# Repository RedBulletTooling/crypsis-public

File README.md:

This project has been created and developed by Matthijs Vogel and Luc Pluimakers.

# Contents of repo
This repo contains all hardware and software files to recreate Crypsis.

Detailed documenatation can be found on our gitbook link here: https://redbullettooling.gitbook.io/keyvilboard-apt/

# Motivation
We would hate to see the knowledge that we build up gone to waste, given we decided to halt this product. This product has not been as commercially viable as we had hoped. But we have put time, effort and a decent chunk of money into this project to create something that hasn't been replicated since. Our goal with publicizing this project is that goal of it's creation will be reached. To prevent harms to those who can't protect themselves. May that be terrorism, child exploitation or other crimes. If you work for an organisation that has these same goals and have a need, contact us. We are happy to help.

# What is Crypsis
Crypsis is a hardware keylogger that communicates using a NFR9160 module. By doing so we can do very advanced methods of communicating covertly, aswell as propper implementation of encryption and other security measures. Apart from the hardware the server is dockerized, meaning it's modular and highly adjustable.

Copied from our website (menura.org);

Hardware
- Every chip, fully programmable, fully open-source. 4G (NB-iot/LTE-M) with encrypted TLS/SSL communication and authentication.
- Secure modem with the latest anti-tamper measurements.
- Only communicate, when you want it. True silent mode, undectectable on the RF spectrum.
- Remotely disable the keyboard for damage prevention on entry.

Software
- Fully dockerized server setup, fully open-source. Setup a standalone Crypsis C2 in under minutes.
- Customize and integrate the API to your needs.
- Everything encrypted, with integrated TLS/SSL based authentication.
- Server infrastructure is modular. The direct communication server can be placed in the target country, whilst all sensitive datastorage is kept within your own borders.

USB
- Crypsis device that sits between the PC USB and the USB cable of the keyboard.

Embedded
- Crypsis device that is integrated in the keyboard of choice with soldering. Keep in mind you have to be directly on the USB bus of the keyboard.

# Disclaimer

The code was still heavily under development and under testing (alpha), before deciding to stall the project. There are serious security issues present in this repository. Think, weak default passwords or injection vulnerabilities. Expect potential issues / conflicts.

Apache2 license applies.

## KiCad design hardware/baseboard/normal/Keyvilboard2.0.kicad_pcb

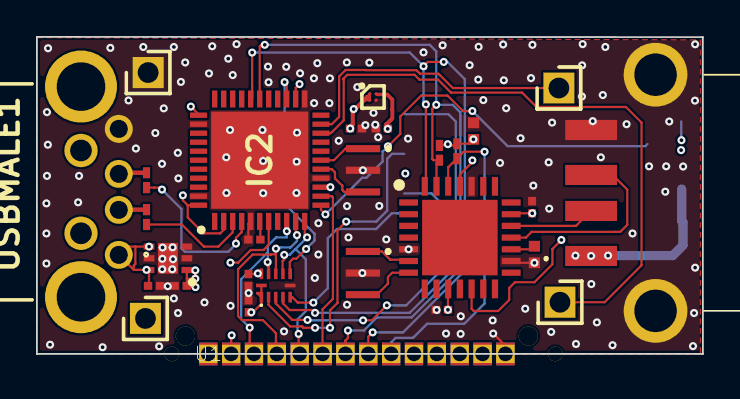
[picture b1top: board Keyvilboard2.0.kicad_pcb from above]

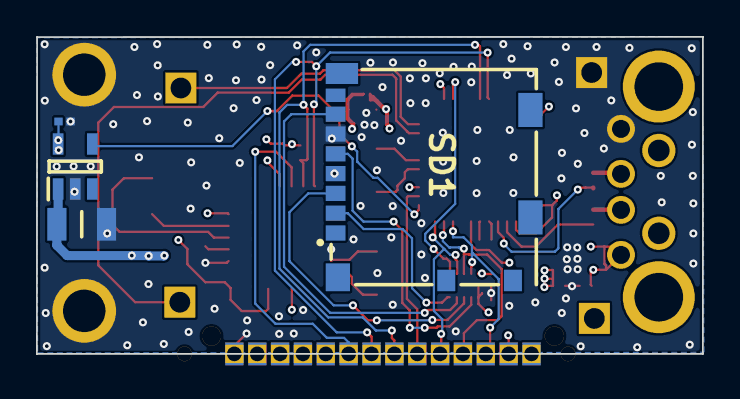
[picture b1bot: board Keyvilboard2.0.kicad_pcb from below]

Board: 4 copper layers, 37.0 x 17.6 mm, 33 parts (4 on the bottom side), 32 nets.

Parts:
0.1uF1, 0.1uF2, 0.1uF5: 02016D104KAT2A; CAPC0603X33N
0.1uF3, 0.1uF4, 1uF1, 1uF2, 1uF3, 1uF4, 1uF5: GRM033C80J105ME05D; CAPC0603X33N
5V+1: 4-103327-3; HDRV1W66P0X254_1X1_213X234X813P
10KOhm1, 10KOhm2: ERA-1AEB103C; RESC0603X26N
10uF1, 10uF2: GRM155C80J106ME11D; CAPC1005X55N
16Mhz1, 16Mhz2: CSTNE16M0VH3C000R0
22Ohm1, 22Ohm2: RC0201JR-7D22RL; RESC0603X26N
C1: GRM31CR60J157ME11L; CAPC3216X180N
GND1: 4-103327-3; HDRV1W66P0X254_1X1_213X234X813P
IC2: ATMEGA32U4-MU; QFN50P700X700X100-45N-D
IC3: PIC24FJ64GB002-I_ML; QFN65P600X600X100-29N-D
IC4: TCR5RG33A,LF; BGA4C35P2X2_64X64X33
IC5: TXB0104RUTR_0; TXB0104RUTR
KEYPWR1: TPS2041CDBVT; SOT95P280X145-5N
PS1: LP5912-5.0DRVR; SON65P200X200X80-7N
RX1: 4-103327-3; HDRV1W66P0X254_1X1_213X234X813P
SD1: 104031-0811; 1040310811
TX1: 4-103327-3; HDRV1W66P0X254_1X1_213X234X813P
U1: EC14-2AP
USBFEMALE1: 87583-2010RLF; 875832010RLF
USBMALE1: UP2-AH-1-TH

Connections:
+3V3: 0.1uF1.1, 0.1uF3.2, 0.1uF4.1, 1uF4.2, 10KOhm1.1, 10KOhm2.2, 10uF2.1, IC3.10, IC3.20, IC3.25, IC4.A2, IC5.1, IC5.12, IC5.13, SD1.4, U1.2
+5V: 1uF3.2, 5V+1.1, PS1.4, PS1.6, USBMALE1.1
CLK: IC5.2, SD1.5
CS: IC5.5, SD1.2
D11: IC2.12, KEYPWR1.4
D+AT: 22Ohm2.1, USBMALE1.3
D+US: IC3.18, USBFEMALE1.3
D-AT: 22Ohm1.1, USBMALE1.2
D-US: IC3.19, USBFEMALE1.2
DI: IC5.3, SD1.3
DO: IC5.4, SD1.7
GND: 0.1uF1.2, 0.1uF2.2, 0.1uF3.1, 0.1uF4.2, 0.1uF5.2, 1uF1.1, 1uF2.1, 1uF3.1, 1uF4.1, 1uF5.1, 10uF1.2, 10uF2.2, 16Mhz1.2, 16Mhz2.2, C1.2, GND1.1, IC2.5, IC2.15, IC2.23, IC2.35, IC2.43, IC2.45, IC3.5, IC3.16, IC3.24, IC4.B2, IC5.6, KEYPWR1.2, PS1.2, PS1.3, PS1.5, PS1.7, SD1.6, U1.14, USBFEMALE1.4, USBFEMALE1.MH1, USBFEMALE1.MH2, USBMALE1.4
MCLR: 10KOhm2.1, IC3.26, U1.9
MISO: IC2.11, IC5.8, U1.5
MOSI: IC2.10, IC5.9, U1.4
NRFRX: IC2.20, RX1.1
NRFTX: IC2.21, TX1.1
unnamed: 1uF1.2, IC2.6
unnamed: 10uF1.1, IC3.17
unnamed: 16Mhz1.1, IC2.17
unnamed: 16Mhz1.3, IC2.16
unnamed: 16Mhz2.1, IC3.6
unnamed: 16Mhz2.3, IC3.7
unnamed: 22Ohm1.2, IC2.3
unnamed: 22Ohm2.2, IC2.4
RST: IC2.13, U1.6
RXUSBH-PGRDATA: 10KOhm1.2, IC2.28, IC3.27, U1.7
SCLK: IC2.9, IC5.10, U1.3
SS: IC2.25, IC5.7
TXUSBH-PGRCLK: IC2.29, IC3.28, U1.8
VCC: 0.1uF2.1, 0.1uF5.1, 1uF2.2, 1uF5.2, IC2.2, IC2.7, IC2.14, IC2.24, IC2.34, IC2.44, IC3.12, IC4.A1, IC4.B1, IC5.11, KEYPWR1.5, PS1.1, U1.1
VDC: C1.1, KEYPWR1.1, USBFEMALE1.1

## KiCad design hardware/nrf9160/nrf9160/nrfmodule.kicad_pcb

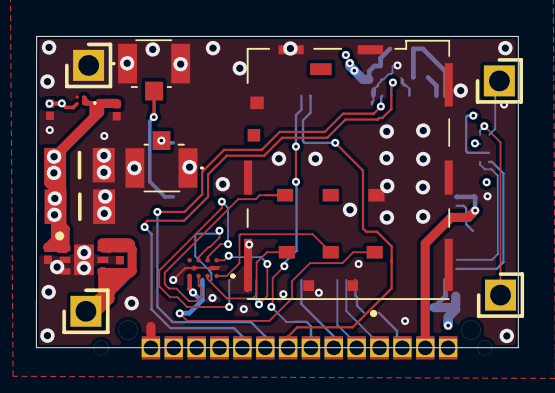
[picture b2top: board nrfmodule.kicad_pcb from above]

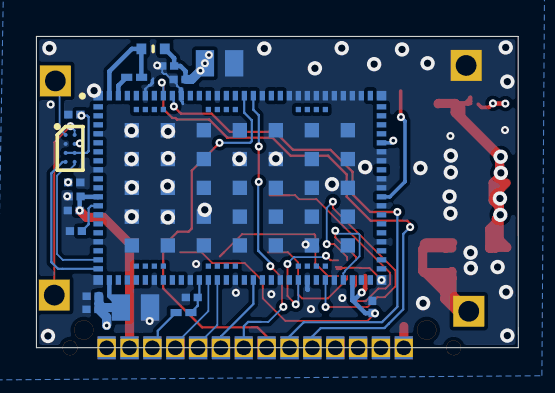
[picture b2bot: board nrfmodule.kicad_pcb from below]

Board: 4 copper layers, 26.8 x 17.3 mm, 35 parts (19 on the bottom side), 29 nets.

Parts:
0,1uF1, 0,1uF2: 02016D104KAT2A; CAPC0603X33N
1uF1, 1uF2, 1uF3, 1uF4, 1uF5: GRM033C80J105ME05D; CAPC0603X33N
4.7uF3, 4.7uF4: GRM035R60J475ME15D; CAPC0603X55N
5.0V1: LP5912-5.0DRVR; SON65P200X200X80-7N
5V+1: 4-103327-3; HDRV1W66P0X254_1X1_213X234X813P
10KOhm1: ERA-1AEB103C; RESC0603X26N
15pF1, 15pF2: 885392004002; CAPC0603X33N
47uF1, 47uF2: 0805ZD476MAT2A; CAPC2012X152N
100nF1, 100nF2, 100nF3, 100nF4: GRM033R60J104KE19J; CAPC0603X33N
220uF1, 220uF2: GRM31CR60J227ME11L; CAPC3216X190N
Edge_Connect1: EC14-2AP
FL1: MMZ1005S121HTD25; BEADC1005X55N
GND1: 4-103327-3; HDRV1W66P0X254_1X1_213X234X813P
IC1: TCR5RG18A,LF; TCR5RG18ALF
NANOSIM1: SF72S006VBDR2500; SF72S006VBAR2500
NRF91: NRF9160-SICA-B1A-R; XCVR_NRF9160-SICA-R
R5: CR0201AFW-1001GLF; RESC0603X26N
RX1: 4-103327-3; HDRV1W66P0X254_1X1_213X234X813P
SIMESDPROTECT1: CM1402-03CP; CM140203CP
TX1: 4-103327-3; HDRV1W66P0X254_1X1_213X234X813P
TXB102: TXB0102YZPR; BGA8C50P2X4_89X189X50
U.FL1, U.FL2: U.FL-R-SMT_10_; UFLRSMT10

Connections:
+1V8: 0,1uF2.1, 1uF1.2, 4.7uF3.1, 100nF3.1, Edge_Connect1.2, IC1.A2, NRF91.12, TXB102.C1, TXB102.C2
+5V: 1uF4.1, 5.0V1.4, 5.0V1.6, 5V+1.1
CLKSIM: NRF91.46, SIMESDPROTECT1.C2
DATSIM: NRF91.48, SIMESDPROTECT1.C3
GND: 0,1uF1.2, 0,1uF2.2, 1uF1.1, 1uF2.1, 1uF3.2, 1uF4.2, 1uF5.1, 4.7uF3.2, 4.7uF4.2, 5.0V1.2, 5.0V1.3, 5.0V1.5, 5.0V1.7, 15pF1.2, 15pF2.2, 47uF1.2, 47uF2.2, 100nF1.2, 100nF2.2, 100nF3.2, 100nF4.2, 220uF1.1, 220uF2.1, Edge_Connect1.14, GND1.1, IC1.B2, NANOSIM1.C5, NANOSIM1.GND1, NANOSIM1.GND2, NANOSIM1.GND3, NANOSIM1.GND4, NANOSIM1.GND5, NANOSIM1.GND6, NANOSIM1.GND7, NANOSIM1.GND8, NANOSIM1.GND9, NANOSIM1.GND10, NRF91.1, NRF91.5, NRF91.9, NRF91.14, NRF91.17, NRF91.21, NRF91.27, NRF91.31, NRF91.36, NRF91.41, NRF91.44, NRF91.47, NRF91.50, NRF91.52, NRF91.56, NRF91.60, NRF91.62, NRF91.63, NRF91.65, NRF91.66, NRF91.72, NRF91.74, NRF91.75, NRF91.76, NRF91.77, NRF91.78, NRF91.79, NRF91.80, NRF91.81, NRF91.82, NRF91.85, NRF91.90, NRF91.94, NRF91.98, NRF91.103_1, NRF91.103_2, NRF91.103_3, NRF91.103_4, NRF91.103_5, NRF91.103_6, NRF91.103_7, NRF91.103_8, NRF91.103_9, NRF91.103_10, NRF91.103_11, NRF91.103_12, NRF91.103_13, NRF91.103_14, NRF91.103_15, NRF91.103_16, NRF91.103_17, NRF91.103_18, NRF91.103_19, NRF91.103_20, NRF91.103_21, NRF91.103_22, NRF91.103_23, NRF91.103_24, NRF91.103_25, NRF91.103_26, NRF91.103_27, NRF91.103_28, NRF91.103_29, NRF91.103_30, NRF91.103_31, NRF91.103_32, NRF91.103_33, NRF91.103_34, NRF91.103_35, SIMESDPROTECT1.B1, SIMESDPROTECT1.B2, TXB102.B1, U.FL1.1, U.FL1.2, U.FL2.1, U.FL2.2
NRESET: Edge_Connect1.3, R5.1
unnamed: 4.7uF4.1, NRF91.13
unnamed: 10KOhm1.2, NRF91.101
unnamed: 100nF4.1, NRF91.32, R5.2
unnamed: NANOSIM1.C2, SIMESDPROTECT1.A1
unnamed: NANOSIM1.C3, SIMESDPROTECT1.A2
unnamed: NANOSIM1.C7, SIMESDPROTECT1.A3
unnamed: NRF91.6, NRF91.7, NRF91.8, NRF91.10, NRF91.11, NRF91.51, NRF91.68, NRF91.69, NRF91.70, NRF91.71, NRF91.73, NRF91.104, NRF91.105, NRF91.106, NRF91.107, NRF91.108, NRF91.109, NRF91.110, NRF91.111, NRF91.112, NRF91.113, NRF91.114, NRF91.115, NRF91.116, NRF91.117, NRF91.118, NRF91.119, NRF91.120, NRF91.121, NRF91.122, NRF91.123, NRF91.124, NRF91.125, NRF91.126, NRF91.127
unnamed: NRF91.61, U.FL1.3
unnamed: NRF91.67, U.FL2.3
RSTSIM: NRF91.43, SIMESDPROTECT1.C1
RX1: Edge_Connect1.7, NRF91.86
RX2: Edge_Connect1.9, NRF91.95
RXNRF: RX1.1, TXB102.A2
RXNRF1.8v: NRF91.19, TXB102.D2
SIM1.8v: 1uF5.2, NANOSIM1.C1, NRF91.49, SIMESDPROTECT1.A4
SWDCLK: Edge_Connect1.4, NRF91.33
SWDIO: Edge_Connect1.5, NRF91.34
SWO: Edge_Connect1.6, NRF91.38
TX1: Edge_Connect1.8, NRF91.87
TX2: Edge_Connect1.10, NRF91.96
TXNRF: TX1.1, TXB102.A1
TXNRF1.8v: NRF91.20, TXB102.D1
VCC: 0,1uF1.1, 1uF2.2, 1uF3.1, 5.0V1.1, 10KOhm1.1, 15pF1.1, 15pF2.1, 47uF1.1, 47uF2.1, 100nF1.1, 100nF2.1, 220uF1.2, 220uF2.2, Edge_Connect1.1, FL1.1, FL1.2, IC1.A1, IC1.B1, NRF91.22, NRF91.102, TXB102.B2

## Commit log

2022-11-18 Initial Commit Organisation
    Some times you dont exceed at first. Try again.
2022-11-18 Motivation
2022-11-19 add server software and clean languague up
2022-11-19 add additional information from website as to what crypsis is
2022-12-24 Update LICENSE
